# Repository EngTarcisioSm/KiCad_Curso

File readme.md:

# KICAD

## SUMÁRIO
- [CARACTERISTICAS DO SOFTWARE](#CARACTERISTICAS-DO-SOFTWARE)
- [DOWNLOAD DO SOFTWARE](#DOWNLOAD-DO-SOFTWARE)
- [CRIANDO UM NOVO PROJETO](#CRIANDO-UM-NOVO-PROJETO)
    - [Adicionar Componente ](#Adicionar-Componente)
    - [Rotacionar componente](#Rotacionar-componente)
    - [Duplicar Componente](#Duplicar-Componente)
    - [Mover Componentes ](#Mover-Componentes)
- [DIAGRAMAS ESQUEMATICOS](#DIAGRAMAS-ESQUEMATICOS)
    - [Projeto Astável 555](#Projeto-Astável-555)
    - [Inserir Alimentação ao circuito e o GND](#Inserir-Alimentação-ao-circuito-e-o-GND)
    - [Inserir wire](#Inserir-wire)
    - [Mover Componente sem perder a linha](#Mover-Componente-sem-perder-a-linha)
    - [Rotações do compotente sobre eixos X e Y](#Rotações-do-compotente-sobre-eixos-X-e-Y)
    - [Alterar o Nome e valores dos componentes](#Alterar-o-Nome-e-valores-dos-componentes)
    - [Anotate do Diagrama Esquemático](#Anotate-do-Diagrama-Esquemático)
    - [Achar Componente mais rápido](#Achar-Componente-mais-rápido)
    - [Organização Profissional de esquemáticos](#organização-profissional-de-esquemáticos)
    - [Método para simular circuitos](#método-para-simular-circuitos)
    - [Criando novos componentes e bibliotecas](#criando-novos-componentes-e-bibliotecas)
    - [Exportando seus esquemáticos profissionais](#Exportando-seus-esquemáticos-profissionais)
- [PLACA DE CIRCUITO IMPRESSO](#PLACA-DE-CIRCUITO-IMPRESSO)
    - [Criando o primeiro lay-out de PCB em face simples](#Criando-o-primeiro-lay-out-de-PCB-em-face-simples)

- [OBSERVAÇÕES](#OBSERVAÇÕES)

## CARACTERISTICAS DO SOFTWARE
- Multiplataforma 
    - Windows 
    - Linux
    - Mac
    - ...
- Gratuito e Ilimitado
- Extensão dos arquivos esquemáticos são ".sch"
- Extensão do layout ".kicad_pcb"
- Possui simulador (não tão eficiente)
<br>[↑](#SUMÁRIO)

## DOWNLOAD DO SOFTWARE
- Site:
    - https://www.kicad.org/
    - Link recomendado: CERN
<br>[↑](#SUMÁRIO)

## CRIANDO UM NOVO PROJETO
- Caminho 
    - File > New > Project ou File > New Project
    - Em arquivos do projeto é gerado uma arvore de arquivos com os formatos kicad_sch e kocad_pcb
- Edição e configuração do arquivo de esquema eletrico 
    - Duplo clique sobre o arquivo com extensão kicad_sch
- Configurações da Página 
    - Arquivos > Configurações da Página ...
    - Será aberto uma janela para inclusão de dados que irão na legenda no canto inferior da página 
<br>[↑](#SUMÁRIO)

### Adicionar Componente 
- Na tela de elaboração da pcb clicar em "A"(add)
    - Será aberto uma nova janela, onde é possivel selecionar o componente
<br>[↑](#SUMÁRIO)

### Rotacionar componente
- Com o Componente selecionado clicar em "R"(rotate)
<br>[↑](#SUMÁRIO)

### Duplicar Componente 
- Com o cursor sobre o componente clicar "CTRL"+"C" e depois "CTRL"+"V" e posicionar o componete
<br>[↑](#SUMÁRIO)

### Mover Componentes  
- É possivel mover o componente com os direcionais do teclado, (inclusive o cursor);
- Com o cursor sobre o componente, clicar em "M"(move), o componente estará selecionado, a partir disso, alocar o componente na região desejada, ao chegar no local clicar em "ENTER" 
<br>[↑](#SUMÁRIO)

## DIAGRAMAS ESQUEMÁTICOS

### Projeto Astável 555
- Será descrito um passo a passo do desenvolvimento de um projeto simples de um circuito 555 astável;
- Criar novo Projeto 
- File(Arquivos) > Page Settings (Configurações de Página)
    - Configurar data do Projeto 
    - Configurar o tamanho do papel
        - Em geral projetos são feitos em A4
        - Orientação de página em formato paisagem 
    - Escrever o numero da revisão
    - Escrever o título (Nome do projeto)
    - Nome da empresa
    - Compentário1: nome do criador do projeto 
    - Finalização com "ENTER"
- Inserir o componente 555
- Inserir o Power do circuito
- Inserir o GND do circuito
- Conexões 
    - Pin4 em VCC
    - Pin6 em Pin2
- Inserão dos demais componentes para o funcionamento 
- Inserir os valores dos componentes bem como os nome
- Projeto finalizado <br>

<br>[↑](#SUMÁRIO)

### Inserir Alimentação ao circuito e o GND
- A inserão é feita com a tecla "P" do teclado, seguind a isso verificando a tensão desejada 
<br>[↑](#SUMÁRIO)

### Inserir wire
- Pode ser efetuado com a tecla "W"
- Para fazer as quebras em 90° utilizar a tecla "Enter"
<br>[↑](#SUMÁRIO)

### Mover Componente sem perder a linha 
- Utilizar a tecla "G"
<br>[↑](#SUMÁRIO)

### Rotações do compotente sobre eixos X e Y
- Utilizar tecla "X" para o eixo X e a tecla "Y" para o eixo Y com o cursor sobre o componente
<br>[↑](#SUMÁRIO)

### Alterar o Nome e valores dos componentes 
- EM um componente existem dois textos, o texto acima refere-se ao nome e o texto subsequente refere-se ao valor
- Clicando sobre cada um deles com um duplo clique é possivel alterar o nome e o valor 
- A segunda opção para alterar o valor de um componente é com o cursor sobre ele e clicar em "V" 
<br>[↑](#SUMÁRIO)

### Anotate do Diagrama Esquemático
- Dar número aos componentes 
- Geralmente utiliza-se a configuração padrão do proprio KiCad onde a numeração é feita de cima para baixo e da esquerda para a direita 
- O processo é feito no botão abaixo <br> 

- Cada inserção de um componente feito após um anotate é necessário um novo anotate
<br>[↑](#SUMÁRIO)

### Achar Componente mais rápido
- Criar novo Projeto para a aula
    - Configurar o Descritivo do projeto 

- Com o KiCad aberto, ao clicar em "A", será aberto uma nova janela com todos os componentes disponiveis para o KiCad

- No espaço filtro digitando apenas uma letra é possivel encontrar de forma rápida alguns compenetes 
    - "r" resistor
    - "c" capacitor
    - "l" indutor
    - "c_p" capacitor polarizado
    - "crys cristal
<br>[↑](#SUMÁRIO)

### Organização Profissional de esquemáticos
- Em eletronica analógica pura, existe uma metodologia um pouco diferente de ligação em relação a circuitos da eletronica digital ou circuitos microcontrolados ou microprocessados
- Exemplo Quarto_Organização_Analogico
    - Amplificador com duplo car diferencial (Circuito amplificador de audio)
    - Não é comum trabalhar com labels(nets com nomes que definem conexão de um ponto a outro do esquemático) em eletronica analógica  
    - É interessante posicionar os componentes mais proximos um do outro quanto possivel 
    - Labels de alimentação e GND são permitidas
    - Procure deixar nivelado as alimentações e os GND
    - Buscar sempre a simetria nos desenhos dos componentes  

- Exemplo Quinto_Organização_Microprocessado
    - Utilizar labels, para cria-las pressionar a tecla "L"
        - Por mais que fisicamente no desenho não exista a conexão o programa entende que existe sim aquela conexão fisica 
    - É interessante separar trechos do circuito com linhas tracejadas que são feitas com o a tecla "I" ou no botão descrito abaixo

    - Observando o seguinte aspecto conforme exemplo abaixo:<br>

    - As labels podem ser colocadas sobre as wires conforme acima 
<br>[↑](#SUMÁRIO)

### Método para simular circuitos 
- A simulação fornecida pelo KiCad é muito simples e bem superficial, não sendo a melhor forma de para análise;
- O teste do simulador será feito atraves do projeto  "Sexto_Simul_Test";
    - Circuito resistivo<br> 
    
- A ferramenta de simulação fica em Tools > Simulator ou em Inspecione > Simulador
- O KiCad possui uma ferramenta de port do circuito criado para o LT Spice que é uma ferramenta de simulação apropriada. Para fazer a conversão ir em Arquivo > Exportar > Exporte a Netlist
    - Apagar a mensagem descrita no campo "Comando externo do simulador" e clicar em "Exporte a Netlist"
    - Será salvo um arquivo com extensão .cir
<br>[↑](#SUMÁRIO)

### Criando novos componentes e bibliotecas
- É possivel criar e editar componentes já existentes 
- Para iniciar a criação de um novo componente na janela principal do KiCad clicar em:
    - Editor de símbolos<br>
    
    - Será aberto uma nova janela 
- É possivel ao criar um novo componente, salva-lo em uma biblioteca já existente ou criar uma nova biblioteca para armazenar o componente 

- Para criar uma nova biblioteca, clicar em Arquivo > Nova Biblioteca, em seguida será solicitado um nome para a bilbioteca 

- Para criar um novo símbolo clicar em "Criar Novo Símbolo" ou digitar a tecla "N"<br>

    - Para criar um novo símbolo é necessário antes criar uma nova biblioteca, aparentemente não se pode criar simbolos em bibliotecas já existentes do kicad;
    - Deve-se selecionar a biblioteca a qual o componente será alocado e depois clicar em "Criar Novo Símbolo";<br>
    
    - Em "Nome do símbolo" inserir o nome do componente;
    - Designador de referência padrão pode ser deixado como "U" bem como "A quantidade das unidades por pacote" como "1"
    - Feito isso clicar em "OK" e será apresentado o nome do componente na tela bem como sua letra de referencia (tudo junto);<br>
    
    - movido 
    
- Feito os passos acima é necessário adicionar os pinos (TODOS DE PREFERENCIA, UM POR UM, DEPOIS É POSSIVEL ORGANIZA-LOS)
    - A adição pode ser feita de duas formas, clicando no icone de adicionar pinos ou clicando em "P"<br>
    
    - Será aberto a seguinte janela para configuração do pino;<br>
    
    - É importante configurar os pinos na nova janela:
        - "Nome do pino"
        - "Numero do Pino"
        - "Tipo elétrico" colocar bidirecional, (APENAS NÃO COLOCA-LO COMO BIDIRECIONAL QUANDO SOUBER EXATAMENTE DO QUE SE TRATA O PINO)
- As bolinhas em cada pino representa a conexão externa do circuito integrado denvendo elas ficarem para foram 
- Criado todos os pinos se faz necessário a sua organização, recomenda-se conforme o descrito no datasheet do componente:
- Descritivo do componente<br>

- Após a organização criar o retangulo para efetuar o contorno com a ferramenta "Adicionar retangulo<br>

- Apos isso clicar com o botão direito sobre a linha do retangulo, ir em propriedade e selecionar "Preencha com a cor de fundo do corpo"
- Ficando da seguinte forma:<br>

- Feito isso basta salvar e o componente ja estará pronto para uso 
<br>[↑](#SUMÁRIO)

### Exportando seus esquemáticos profissionais
- Gerar o pdf do esquemático
- Para gerar o pdf será utilizado o projeto no qual foi desenvolvido o amplificador 
- Para gerar o esquemático clicar em "Plot"<br>

- Na janela aberta é possivel escolher o diretorio em que será salvo, o formato de saida, o tamanho da folha e se colorido e preto e branco 

    - Em geral pdf de esquemáticos são colocados em preto e branco
- Observação: Caso deseje-se gerar mais de um arquivo (preto e branco e colorido) acarretará em um erro pois não é possivel configurar o nome do arquivo de saída. Para não ocorrer o arquivo gerado deve ser mudado de diretorio 
<br>[↑](#SUMÁRIO)

## PLACA DE CIRCUITO IMPRESSO
- Projetos em face simples;
- Dupla face;
- Com circuitos smd;
- Criação de footprint específicas para componentes, caso não exista na biblioteca padrão;
- Geração dos arquivos gerber;
<br>[↑](#SUMÁRIO)

### Criando o primeiro lay-out de PCB em face simples 
- Projeto de um regulador de 5V
    - Os capacitores de entrada são para filtragem do sinal de entrada em especial o eletrolítico
    - O Resistor na saída é limitante de corrente para o led indicador de funcionamento<br>
    
    - Dar o anotate no circuito para numerar os componentes 
- Após o esquema elétrico montado deve-se verificar algum erro de conexão eletrica indo em Inspecione > Verificador das Regras elétricas
    - Será apresentado alguns erros nesse caso entretanto os erros não devem ser levados em consideração
- Após a analise em cima  efetuar a atribuição dos footprints em "Executa a ferramenta de atribuição de footprint"<br>

- Será aberto uma nova janela para fazer associação de footprints a cada componente, nesse momento é necessário de ter o conhecimento de cada componente utilizado  
    - É necessário escolher a biblioteca de footprint a esquerda e as medições do footprints filtrados a direita, ao escolher dar um duplo clique 
    - Finalizando o processo a janela ficaria como abaixo;<br>
    
    - Ao finalizar clicar em "Aplique, Salve o Esquema & Continue"
- Ao que parece a partir da versão 6 do KiCad a geração de netList não é necessária, após o passo anterior, clicar em "Abra a PCI no editor"<br>

- Na nova Janela aberta, clicar em "Update PCB with changes made to schematic"<br>

    - Todos os componentes serão colocados na folha, deve-se arrastalos para o meio e deve-se organiza-los
    - Os mesmos comandos de organização no editor de esquema também se aplicam aqui (movimento, rotação e etcm)<br>
    
- Desenhar as layers
    - Como se trata de uma placa de face simples selecionar na aba Aparence layers > B.Cu<br>
    
    - Seguido a isso clicar em "Route Track" e a partir disso desenhar as layers acompanhando os riscos brancos do desenho<br>
    <br>
    
- Desenhar o contorno da placa 
    - Selecionar "Edge.Cuts na mesma Guia Aparence layers
- Para verificar o tamanho da placa selecionar a unidade de medida a esquerda e em seguida utilizar o botão de medição a direita<br>
<br> 
<br> 
- É possivel visualizar através de uma animação 3d o resultado clocando em View > 3D Viewer<br>
<br> 
<br>[↑](#SUMÁRIO)

### Criando o primeiro lay-out de PCB em dupla face
- Placas em dupla face de esquemas intermediários a avançados minimiza indutancias e capacitancias parasitas (trilhas longas ou paralelas);
- Para efeturar trilhas superiores ou seja na outra face, utilizar "F.Cu", sendo um tracejado vermelho
- Para adicionar os furos de passagem de trilha de uma face para outra, ao fazer a trilha basta pressionar a tecla "V"
- Fazer o contorno de corte da placa com Edge.Cuts
- Após efetuar todas as trilhas verificar se existe algum problema encontrado, clicando em Inspecione > Verificador das Regras do Desenho
- Para fazer escritas na placa escolha F.SilkScreen

- Para adicionar os furos de fixação clicar no icone "Adicionar um Footprint" ou clicar em A;
- Escolher o furo de prefernecia, ( no caso ado autor MountingHole 3.2,,_M3)

### Criando lay-out em SMD
- Para um circuito compacto, é necessário desenvolver a placa de circuito impreso com componentes SMD;
- Nono Projeto
- Para trabalhar em smd o primeiro passo é desenvolver o esquemático normalmente
- Após todo o desenvolvimento normalmente efetuado, basta clicar na ferramenta "Executar a ferramenta de atribuição de footprint (versão 6.0 kicad)" e escolher os componentes smd que serão utilizados
- Associar todos os footprints dos componentes que podem ser SMD
    <br> 
    - O kicad não faz associação automática de footprints a componentes, para isso deve-se acessar o datasheet do componente e verificar as especificações de tamanho e tipo de soquete do componente e efetuar manualmente esse processo
- Após o processo acima, salvar as associações retornar para a folha de projeto e clicar em "Abra a PCI no editor da placa (versão Kicad 6.0)"
- Na nova janela clicar em "Update PCB whith changes made to schematic (F8)", os componentes irão para folha;
- Organizar os componentes
- Observação, o componente TL084 ja possui internamente os 4 circuitos necessários, logo no esquema elétrico para sua utilização é necessário nomea-lo como U1 em todos e clicando no componente será aberto uma nova janela onde é possivel escolher os canais para os demais circuitos internos do componente (A,B,C,D)
<br> 
<br> 
- Diferentes das placas pth se começa o desenho das trilhas pelo front cupper (F.Cu)
    - Atalho para esse desenho a tecla "X"

- Após o desenho de todas as trilhas clicar no botão "Mostrar a janela do verificador das regras do desenho"
<br> 
    - É informado na janela erros e inclusive conexões faltantes 

- Para Economizar material corrosivo inclusive inserir fornecer uma proteção a placa do ponto de vista elétrico é possivel nos pontos que não há trilha serem inseridos uma conexão com o gnd.
- Para adicionar deve-se clicar no botão "Add a filled zone ou Ctrl + Shift + Z"
<br> 
- Será aberto uma janela na qual deve-se selecionar F.Cu, B.Cu e GND. Será solicitado para que se 
selecione a area. Após isso deve-se clicar dentro da area com o botão direito, ir em "Zonas" e clicar em preencher todas as zonas

### Desenhando footprints personalizados
- Em alguns casos quando o componente não possui footprint é necessário cria-lo;
- O Kicad possui uma ferramenta simples e eficaz para desenhos de footprints;
- Criação exemplo de um componente pth e um smd 
    - Componente PTMM
        - O componente a ser utilizado será o AN7125 (pth)

    - Primeiro passo para a criação é abrir o editor de footprints localizado como um icone na pagina principal do kicad
    <br> 
    - Na janela aberta clicar no icone "Create a new, empty footprint (ctrl + N)
    <br>
    - Na nova janela aberta deve-se dar um nome para o componente e na versão do KiCad nova também é solicitado o tipo de componente
    - É possivel configurar a passada do kiCad para ser algo semelhante ou proximo da passada dos pads do componente facilitando assim o desenho do mesmo. Deve-se clicar com o botão direito ta tela do Kicad na area de desenhor e ir em "Grid" e em seguida efetuar a seleção do novo step
    <br>
    - Para adicionar os furos que o componente possui (PTH) que transpassam a placa, clicar no botão  "Add Pad"
    <br>
    - Para aumentar a espeçura do buraco (recomenda-se sempre que o buraco seja um pouco maior que o conector para que a solda possa entrar ), para configurar isso, clica-se duas vezes sobre o pad e se altera Pad Size X para determinar o tamanho da região de conexão com as trilhas e em Hole size x para alterar o tamanho do buraco 

    - O Buraco possui uma camada redonda, entretanto convenciona-se que o pino 1 do componente a sua regiao em torno do buraco não seja redonda mais sim quadrado 

    - É importante desenhar o contorno do componente com o tipo de linha "F.Silkscreen"

    - Convenciona-se no entorno do primeiro pino desenhar um quadrado, ficando ao final da seguinte forma
    <br>

    - No caso do componente desenhado AN7125 é possivel também desenhar uma região a qual o dissipador estaria posicionado. Ficando ao final conforme abaixo
    <br>

    - Para efetuar desenhos na parte de baixo da placa utiliza-se a layer "B.Silkscreen"

    - Caso o componente possuia uma area para seus pads e uma area maior para o componente em só é possivel defini-la com a layer "F.Courtyard"

    - Para salvar no kicad 6 não é possivel salvar nas bibliotecas ja existentes é necessário criar uma biblioteca nova, clicando em File > New Libraries, em seguida criar uma pasta na qual os footprints serão salvos. Feito isso clicar em SAve As e selecionar a biblioteca criada  

- O Kicad possui uma ferramenta que auxilia na criação de footprints de forma muito mais fácil
- Terá como exemplo a criação de um footprint para o microcontrolador ATMega328P com o encapsulamento TQFP
    - Após criar o projeto do footprint clicar em "Create a new footprint using the Footprint Wizard"
    - Será aberto uma nova janela solicitando como base alguns footprints base, para o exemplo será selecionado o tipo "QFP". Será aberto um footprint base de 100pinos e uma tabela ao lado para configurar o footprint 
    <br>

    - Configurando basta clicar em "Export footprint to editor"

### Gerando o arquivo Gerber para fabricação
- Arquivo necessário para envio para empresas que fabricam placas;
- Antes de gerar o arquivo é interessante verificar se existe algum erro na placa atraves da ferramenta presente no KiCad chamada "Show the design rules checker window"
<br>
- Será aberto uma janela "DRC Control", devendo-se clicar em "Run DRC" para verificar possiveis erros antes de gerar o arquivo de produção
- Para se gerar o arquivo gerber deve-se clicar em plot 
<br>
- Será aberto uma nova janela na qual é solicitado o caminho em que deverá ser salvo o arquivo. Escolhendo a pasta, deve-se apenas clicar em "Plot"
- Após o passo acima clicar em "Generate Drill Files...", será aberto uma nova janela e deve-se clicar em "Generate Drill File"
- Para verificar se os arquivos foram gerados corretamente, na tela principal do KiCad existe um visualizador de arquivos gerber que pode ser utilizado para visualizar o resultado 
<br>
    - Aberto A nova janela basta selecionar os arquivos e visualizar se esta tudo correto 

### Projeto Final: Placa controladora (PIC)

## OBSERVAÇÕES
- Sempre trabalhar com o grid habilitado 
- Optar por trabalhar com medidas em polegadas 
- Help > List HotKeys contem a lista completa de atalhos do KiCad
- É possivel mover o nome do componente assim como é feito com o componente em sí, bastando para isso colocar o cursor sobre o nome e apertar m, efetuando o mesmo processo que é feito com o componente como um todo 
- Segurando "CTRL" e apertando as fechas direita ou esquerda se tem o movimento horizontal no desenho
- Segurando "SHIFT" e apertando para baixo ou para cima se tem o movimento vertical da folha de desenho
- Não é recomendado usar processos de roteamento de trilhas automáticas, o KiCad não possui nativamente essa ferramenta, entretanto não é recomendado seu uso 
- A borda que define as margens da placa é a "Edge.Cuts"
- Alguns componentes possuem mais de um circuito integrado interno como é o caso do nono projeto, para a utilização de todos ele é necessário copia-lo e cola-lo a quantidade de itens a ser utilizado e em seu nome U?X a interrogação, manter o mesmo numero e só alterar o X correspondente a letra. Para alterar a letra basta dar dois cliques no componente e na nova janela ir em General Units e escolher (A, B, C, ...)
<br>[↑](#SUMÁRIO)

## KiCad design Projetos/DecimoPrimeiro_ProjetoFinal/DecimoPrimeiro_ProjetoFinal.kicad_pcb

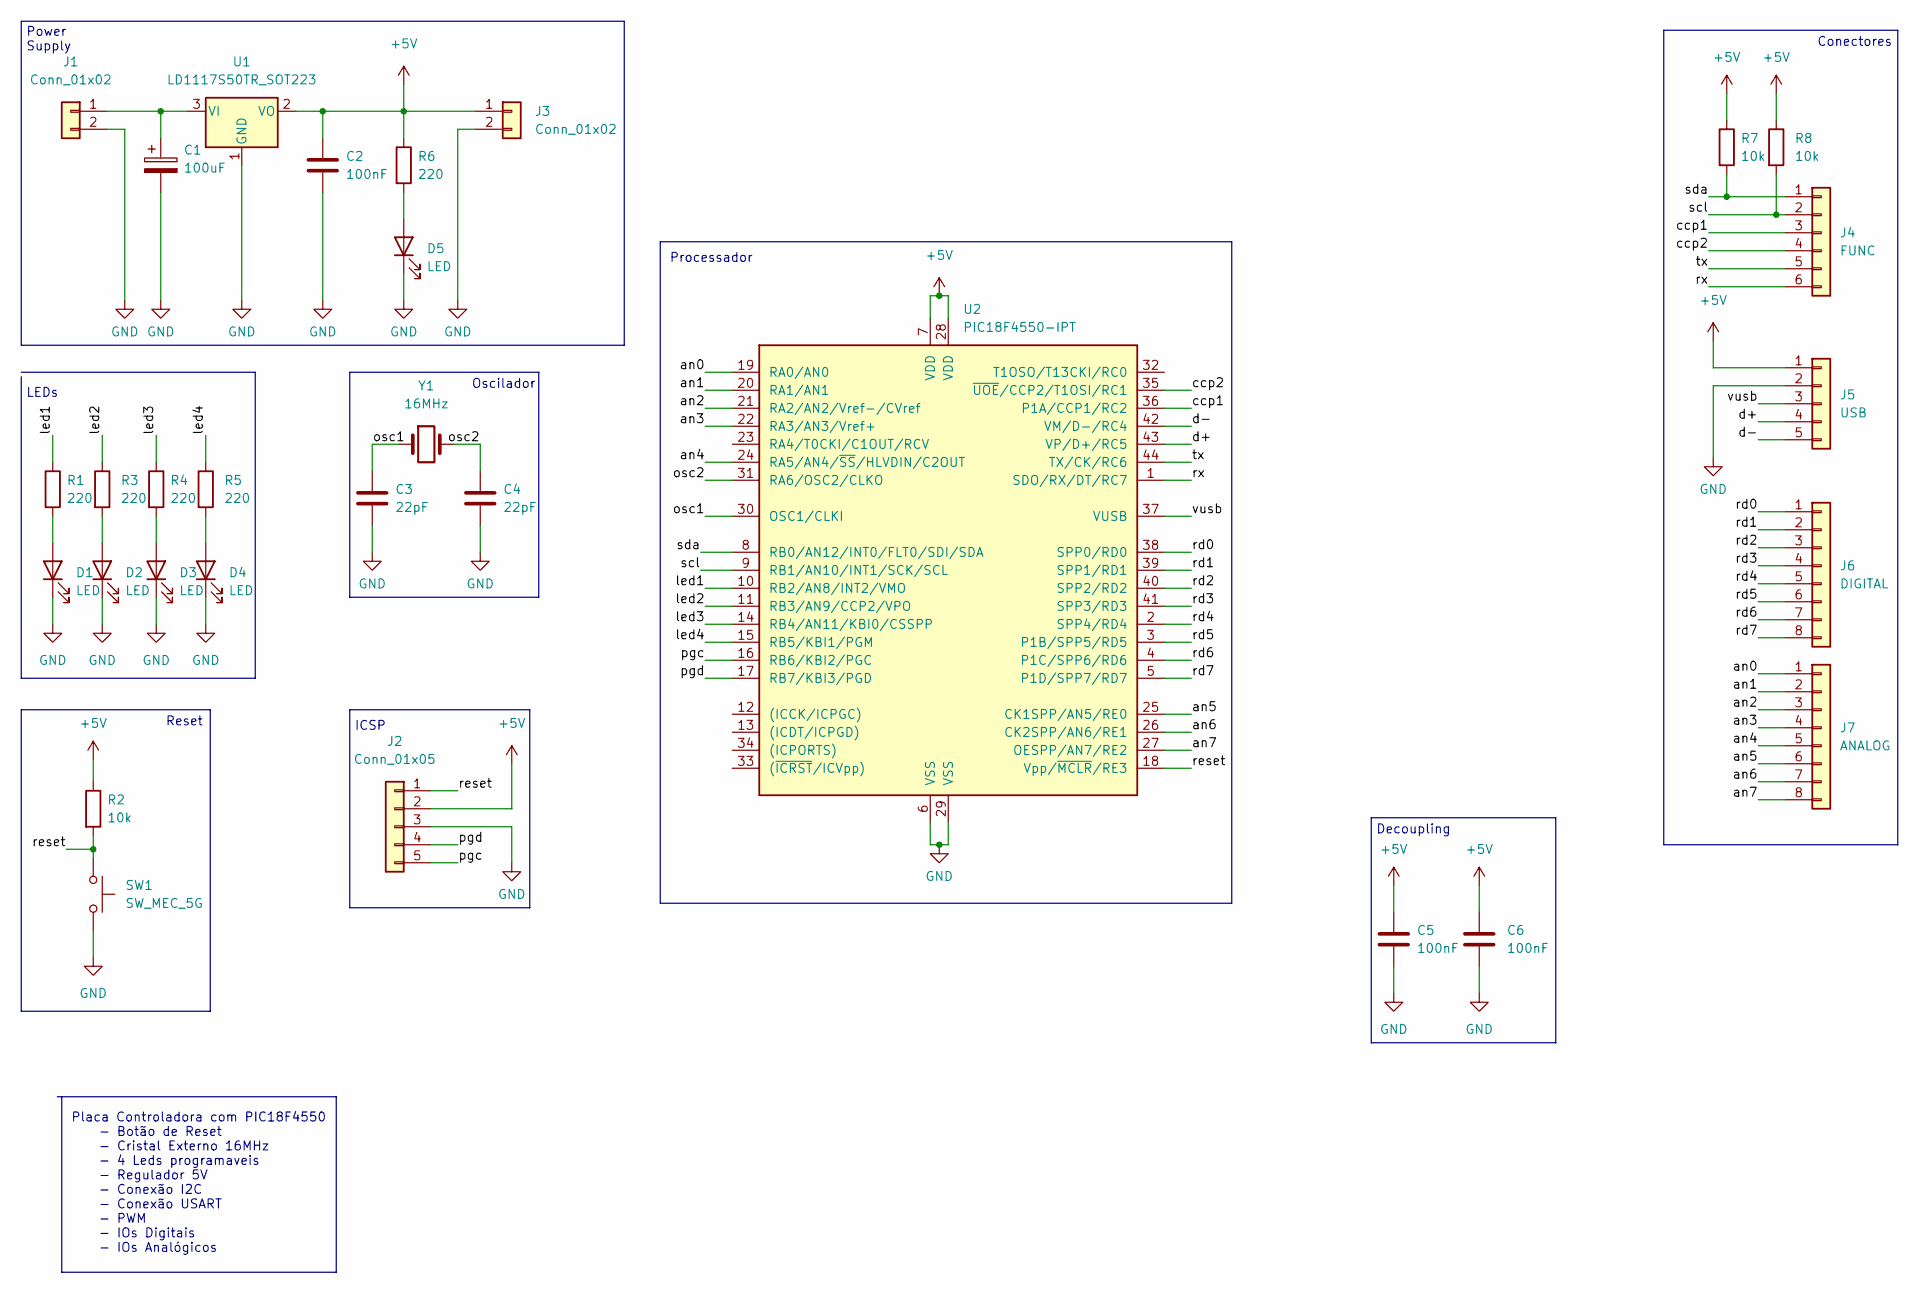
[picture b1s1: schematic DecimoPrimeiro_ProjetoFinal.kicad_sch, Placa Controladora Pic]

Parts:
C1: 100uF; CP_Elec_6.3x7.7
C2, C5, C6: 100nF; C_0805_2012Metric
C3, C4: 22pF; C_0805_2012Metric
D1, D2, D3, D4, D5: LED; LED_0805_2012Metric
J1, J3: Conn_01x02; PinHeader_1x02_P2.54mm_Vertical
J2: Conn_01x05; PinHeader_1x05_P2.54mm_Vertical
J4: FUNC; PinHeader_1x06_P2.54mm_Vertical
J5: USB; PinHeader_1x05_P2.54mm_Vertical
J6: DIGITAL; PinHeader_1x08_P2.54mm_Vertical
J7: ANALOG; PinHeader_1x08_P2.54mm_Vertical
R1, R3, R4, R5, R6: 220; R_0805_2012Metric
R2, R7, R8: 10k; R_0805_2012Metric
SW1: SW_MEC_5G; SW_PUSH_6mm_H4.3mm
U1: LD1117S50TR_SOT223; SOT-223-3_TabPin2
U2: PIC18F4550-IPT; TQFP-44_10x10mm_P0.8mm
Y1: 16MHz; Crystal_HC18-U_Vertical

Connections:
+5V: C2.1, C5.1, C6.1, J2.2, J3.1, J5.1, R2.1, R6.1, R7.1, R8.1, U1.2 (VO), U2.7 (VDD), U2.28 (VDD)
/an0: J7.1, U2.19 (RA0/AN0)
/an1: J7.2, U2.20 (RA1/AN1)
/an2: J7.3, U2.21 (RA2/AN2/Vref-/CVref)
/an3: J7.4, U2.22 (RA3/AN3/Vref+)
/an4: J7.5, U2.24 (RA5/AN4/~SS/HLVDIN/C2OUT)
/an5: J7.6, U2.25 (CK1SPP/AN5/RE0)
/an6: J7.7, U2.26 (CK2SPP/AN6/RE1)
/an7: J7.8, U2.27 (OESPP/AN7/RE2)
/ccp1: J4.3, U2.36 (P1A/CCP1/RC2)
/ccp2: J4.4, U2.35 (~UOE/CCP2/T1OSI/RC1)
/d+: J5.4, U2.43 (VP/D+/RC5)
/d-: J5.5, U2.42 (VM/D-/RC4)
/led1: R1.1, U2.10 (RB2/AN8/INT2/VMO)
/led2: R3.1, U2.11 (RB3/AN9/CCP2/VPO)
/led3: R4.1, U2.14 (RB4/AN11/KBI0/CSSPP)
/led4: R5.1, U2.15 (RB5/KBI1/PGM)
/osc1: C3.1, U2.30 (OSC1/CLKI), Y1.1
/osc2: C4.1, U2.31 (RA6/OSC2/CLKO), Y1.2
/pgc: J2.5, U2.16 (RB6/KBI2/PGC)
/pgd: J2.4, U2.17 (RB7/KBI3/PGD)
/rd0: J6.1, U2.38 (SPP0/RD0)
/rd1: J6.2, U2.39 (SPP1/RD1)
/rd2: J6.3, U2.40 (SPP2/RD2)
/rd3: J6.4, U2.41 (SPP3/RD3)
/rd4: J6.5, U2.2 (SPP4/RD4)
/rd5: J6.6, U2.3 (P1B/SPP5/RD5)
/rd6: J6.7, U2.4 (P1C/SPP6/RD6)
/rd7: J6.8, U2.5 (P1D/SPP7/RD7)
/reset: J2.1, R2.2, SW1.1 (A), SW1.2 (A), U2.18 (Vpp/~MCLR/RE3)
/rx: J4.6, U2.1 (SDO/RX/DT/RC7)
/scl: J4.2, R8.2, U2.9 (RB1/AN10/INT1/SCK/SCL)
/sda: J4.1, R7.2, U2.8 (RB0/AN12/INT0/FLT0/SDI/SDA)
/tx: J4.5, U2.44 (TX/CK/RC6)
/vusb: J5.3, U2.37 (VUSB)
GND: C1.2, C2.2, C3.2, C4.2, C5.2, C6.2, D1.1 (K), D2.1 (K), D3.1 (K), D4.1 (K), D5.1 (K), J1.2, J2.3, J3.2, J5.2, SW1.3 (B), SW1.4 (B), U1.1 (GND), U2.6 (VSS), U2.29 (VSS)
unnamed: C1.1, J1.1, U1.3 (VI)
unnamed: D1.2 (A), R1.2
unnamed: D2.2 (A), R3.2
unnamed: D3.2 (A), R4.2
unnamed: D4.2 (A), R5.2
unnamed: D5.2 (A), R6.2

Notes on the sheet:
ICSP
Oscilador
Processador
Power Supply
Conectores
Decoupling
LEDs
Placa Controladora com PIC18F4550 - Botão de Reset - Cristal Externo 16MHz - 4 Leds programaveis - Regulador 5V - Conexão I2C - Conexão USART - PWM - IOs Digitais - IOs Analógicos
Reset

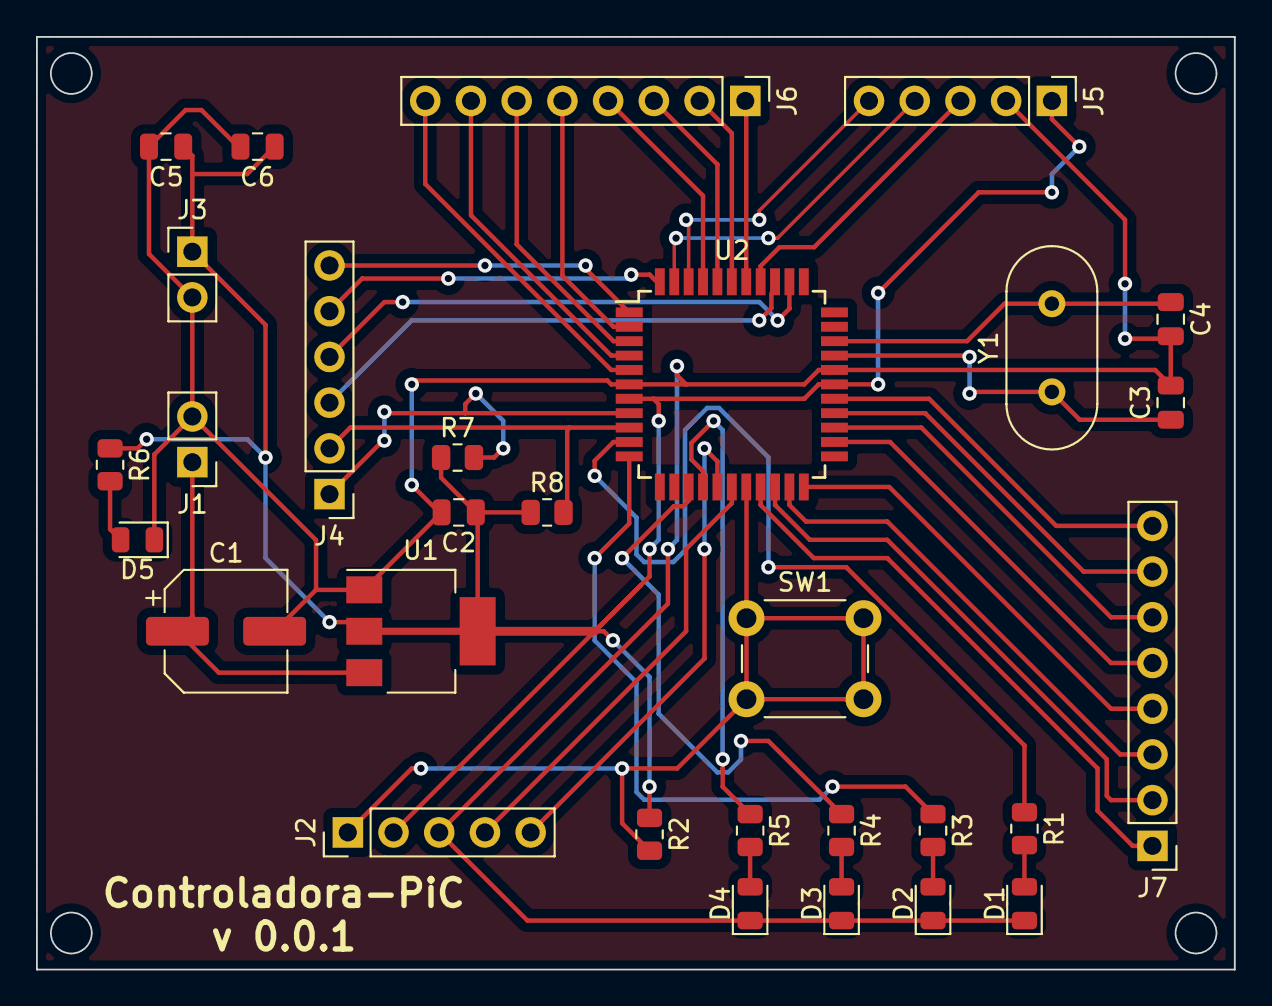
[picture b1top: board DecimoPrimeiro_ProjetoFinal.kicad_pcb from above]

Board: 2 copper layers, 66.5 x 51.8 mm, 30 parts (0 on the bottom side), 42 nets.

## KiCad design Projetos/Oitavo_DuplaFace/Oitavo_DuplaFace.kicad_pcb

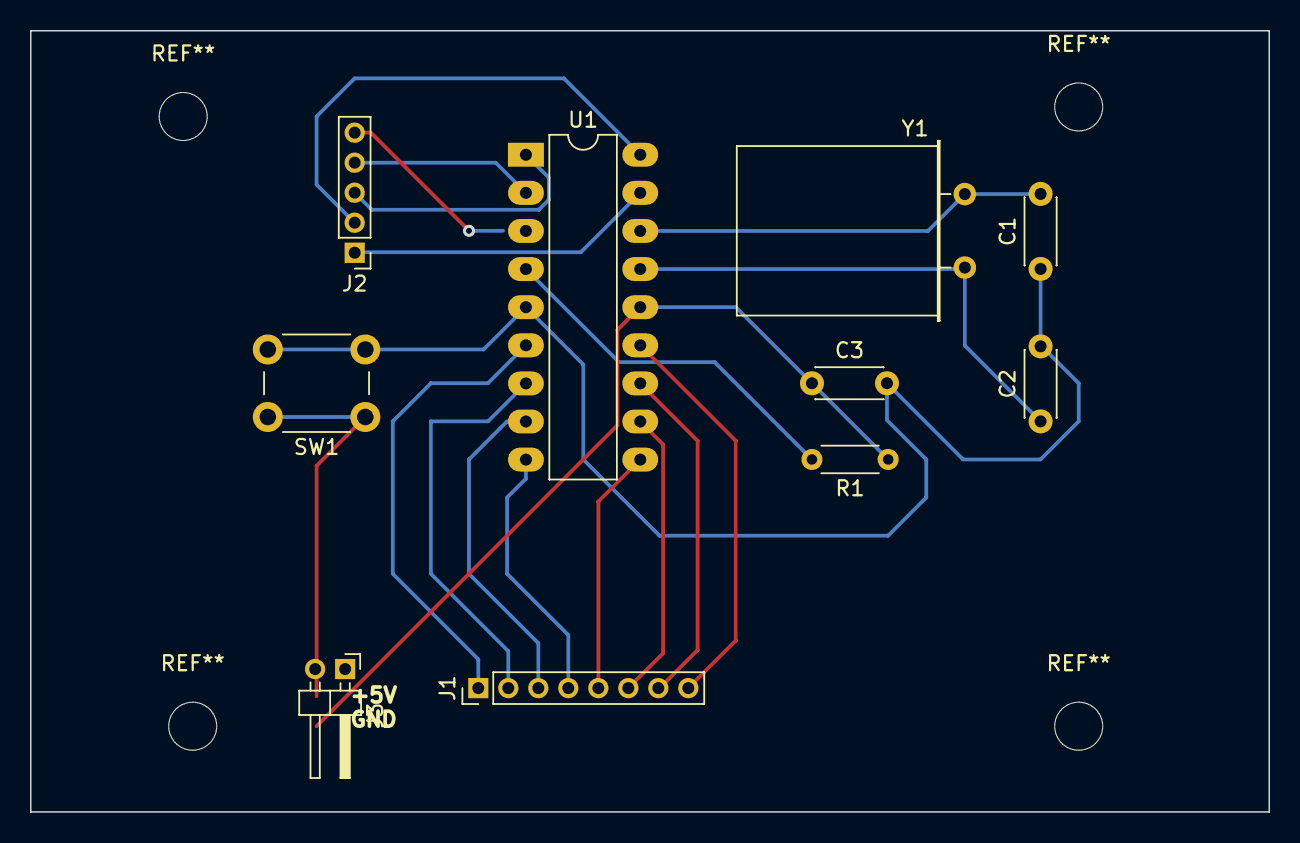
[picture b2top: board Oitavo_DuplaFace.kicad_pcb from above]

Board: 2 copper layers, 82.5 x 52.1 mm, 10 parts (0 on the bottom side), 17 nets.

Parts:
C1, C2: 22pF; C_Disc_D4.3mm_W1.9mm_P5.00mm
C3: 100nF; C_Disc_D4.3mm_W1.9mm_P5.00mm
J1: Conn_01x08; PinHeader_1x08_P2.00mm_Vertical
J2: Conn_01x05; PinHeader_1x05_P2.00mm_Vertical
J3: Conn_01x02; PinHeader_1x02_P2.00mm_Horizontal
R1: 10k; R_Axial_DIN0204_L3.6mm_D1.6mm_P5.08mm_Horizontal
SW1: SW_MEC_5G; SW_PUSH_6mm_H4.3mm
U1: PIC16F628A-IP; DIP-18_W7.62mm_LongPads
Y1: Crystal; Crystal_HC18-U_Horizontal

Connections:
+5V: C3.1, J3.1, R1.1, U1.14 (VDD)
/osc1: C1.2, U1.16 (CLKIN/OSC1/RA7), Y1.1
/osc2: C2.1, U1.15 (CLKOUT/OSC2/RA6), Y1.2
/ra0: J2.1, U1.17 (AN0/RA0)
/ra1: J2.2, U1.18 (AN1/RA1)
/ra2: J2.3, U1.1 (Vref/AN2/RA2)
/ra3: J2.4, U1.2 (CMP1/AN3/RA3)
/rb0: J1.1, U1.6 (RB0/INT)
/rb1: J1.2, U1.7 (RB1/RX/DT)
/rb2: J1.3, U1.8 (RB2/TX/CK)
/rb3: J1.4, U1.9 (RB3/CCP1)
/rb4: J1.5, U1.10 (RB4/PGM)
/rb5: J1.6, U1.11 (RB5)
/rb6: J1.7, U1.12 (RB6/T1OSC0/T1CKI/PGC)
/rb7: J1.8, U1.13 (RB7/T1OSI/PGD)
/reset: R1.2, U1.4 (~MCLR/Vpp/RA5)
GND: C1.1, C2.2, C3.2, J3.2, SW1.1 (A), SW1.2 (A), U1.5 (VSS)

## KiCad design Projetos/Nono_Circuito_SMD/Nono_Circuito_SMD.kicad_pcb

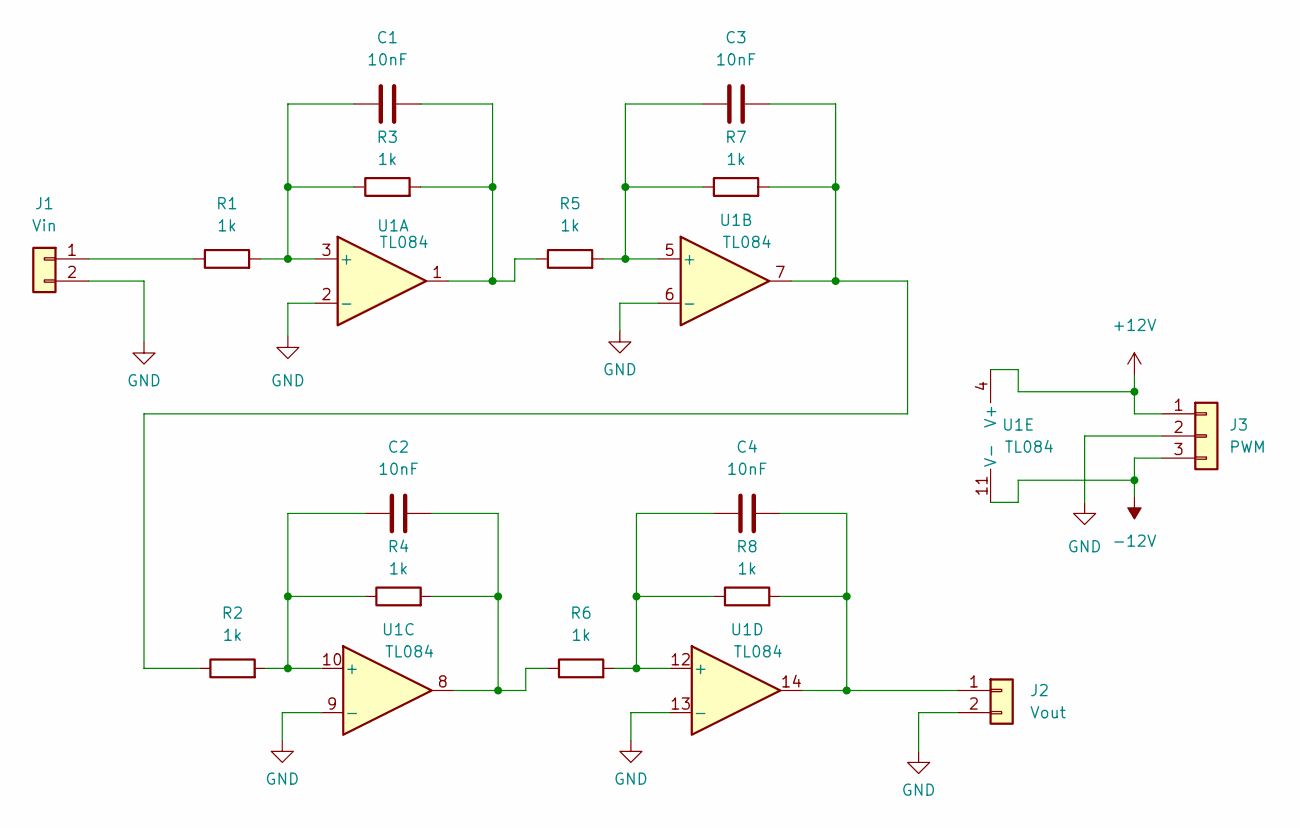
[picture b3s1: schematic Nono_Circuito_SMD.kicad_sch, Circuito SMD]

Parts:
C1, C2, C3, C4: 10nF; C_0805_2012Metric
J1: Vin; PinHeader_1x02_P2.00mm_Vertical
J2: Vout; PinHeader_1x02_P2.00mm_Vertical
J3: PWM; PinHeader_1x03_P2.00mm_Vertical
R1, R2, R3, R4, R5, R6, R7, R8: 1k; R_0805_2012Metric
U1: TL084; TSSOP-14_4.4x5mm_P0.65mm

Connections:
+12V: J3.1, U1.4 (V+)
-12V: J3.3, U1.11 (V-)
GND: J1.2, J2.2, J3.2, U1.2 (-), U1.6 (-), U1.9 (-), U1.13 (-)
unnamed: C1.1, R1.2, R3.1, U1.3 (+)
unnamed: C1.2, R3.2, R5.1, U1.1
unnamed: C2.1, R2.2, R4.1, U1.10 (+)
unnamed: C2.2, R4.2, R6.1, U1.8
unnamed: C3.1, R5.2, R7.1, U1.5 (+)
unnamed: C3.2, R2.1, R7.2, U1.7
unnamed: C4.1, R6.2, R8.1, U1.12 (+)
unnamed: C4.2, J2.1, R8.2, U1.14
unnamed: J1.1, R1.1

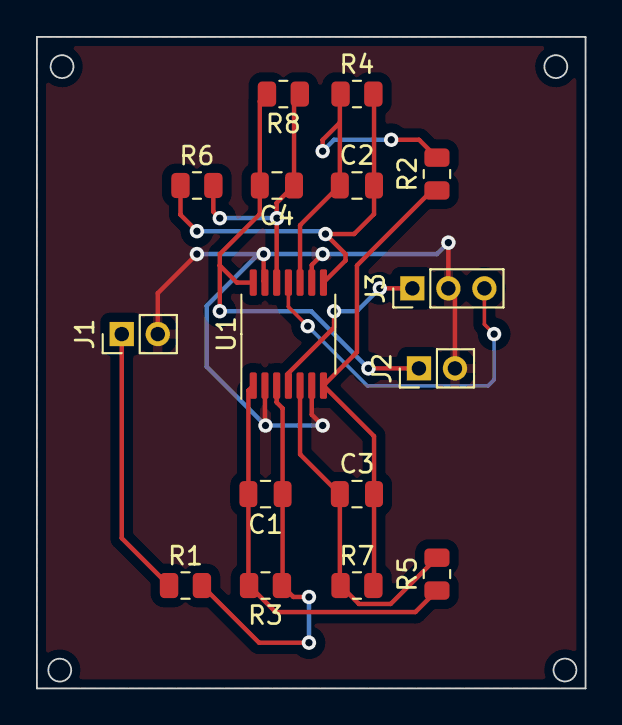
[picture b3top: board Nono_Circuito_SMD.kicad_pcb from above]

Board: 2 copper layers, 30.5 x 36.2 mm, 16 parts (0 on the bottom side), 12 nets.

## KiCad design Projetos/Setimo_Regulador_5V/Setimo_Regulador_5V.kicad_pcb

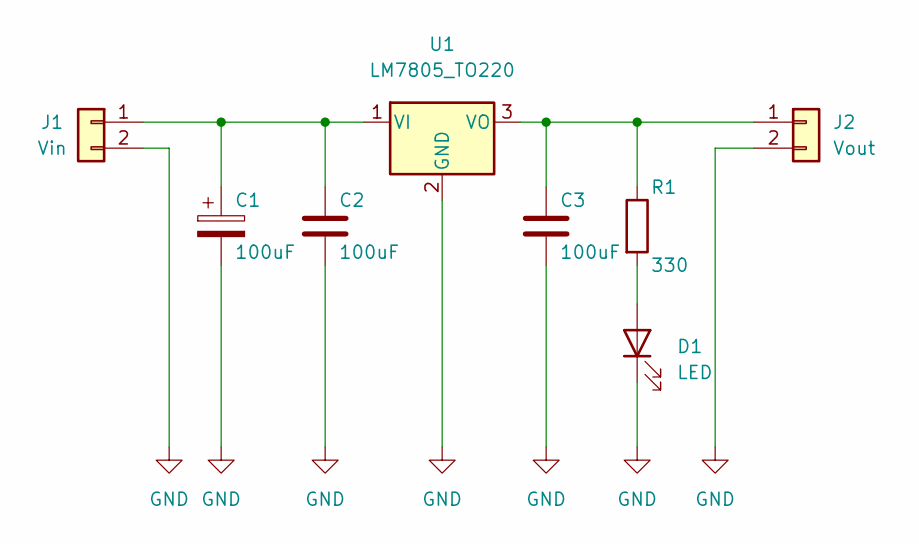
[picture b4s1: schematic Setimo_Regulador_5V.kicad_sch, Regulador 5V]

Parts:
C1: 100uF; CP_Radial_D10.0mm_P3.50mm
C2, C3: 100uF; C_Disc_D5.0mm_W2.5mm_P5.00mm
D1: LED; LED_D5.0mm_IRGrey
J1: Vin; PinHeader_1x02_P2.00mm_Vertical
J2: Vout; PinHeader_1x02_P2.00mm_Vertical
R1: 330; R_Axial_DIN0207_L6.3mm_D2.5mm_P7.62mm_Horizontal
U1: LM7805_TO220; TO-220-3_Vertical

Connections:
GND: C1.2, C2.2, C3.2, D1.1 (K), J1.2, J2.2, U1.2 (GND)
unnamed: C1.1, C2.1, J1.1, U1.1 (VI)
unnamed: C3.1, J2.1, R1.1, U1.3 (VO)
unnamed: D1.2 (A), R1.2

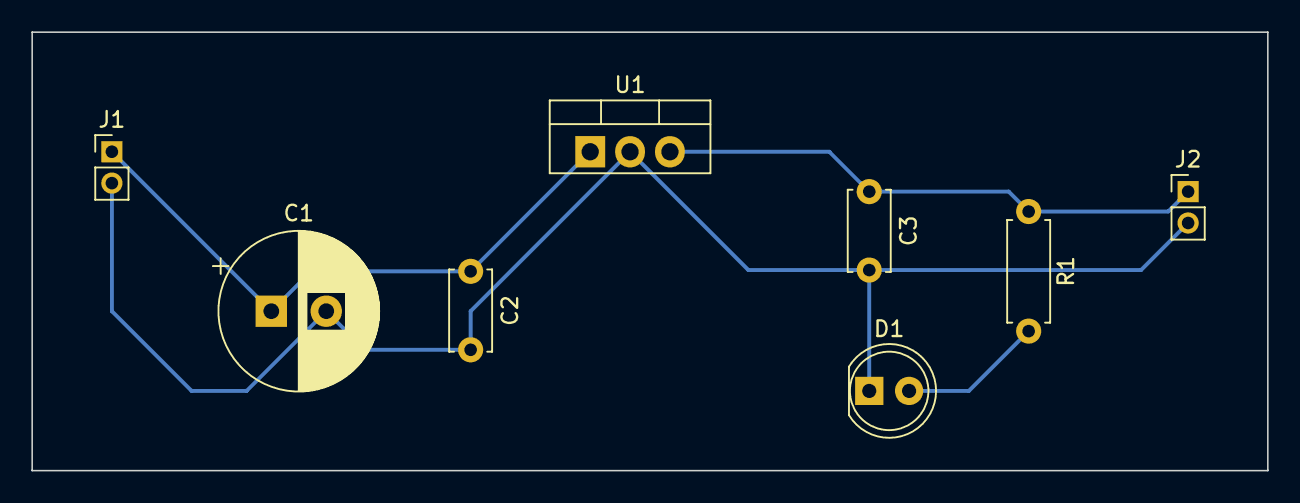
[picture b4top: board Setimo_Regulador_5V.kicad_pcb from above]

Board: 2 copper layers, 78.7 x 27.9 mm, 8 parts (0 on the bottom side), 4 nets.

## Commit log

2022-03-25 second
2022-04-07 att2
2022-06-20 atttttt
